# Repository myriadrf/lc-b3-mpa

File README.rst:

LibreCellular LTE Band 3 Medium Power Amplifier
===============================================

.. image:: https://raw.githubusercontent.com/myriadrf/lc-b3-mpa/main/images/B3MPA_0p1_PCB_1_1280w.jpg
   :alt: Detail of CI hardware.

This repository contains the PCB (KiCAD) and mechanical designs (STEP) for the LTE Band 3 Medium Power Amplifier.

For further details see the `LibreCellular Documentation`_.

Licence
-------

LibreCellular LTE Band 3 Medium Power Amplifier is copyright 2022 AB Open Ltd and provided under the Solderpad Hardware License v2.1.

.. _LibreCellular Documentation: https://librecellular.org/developer/hardware/rf/b3mpa.html

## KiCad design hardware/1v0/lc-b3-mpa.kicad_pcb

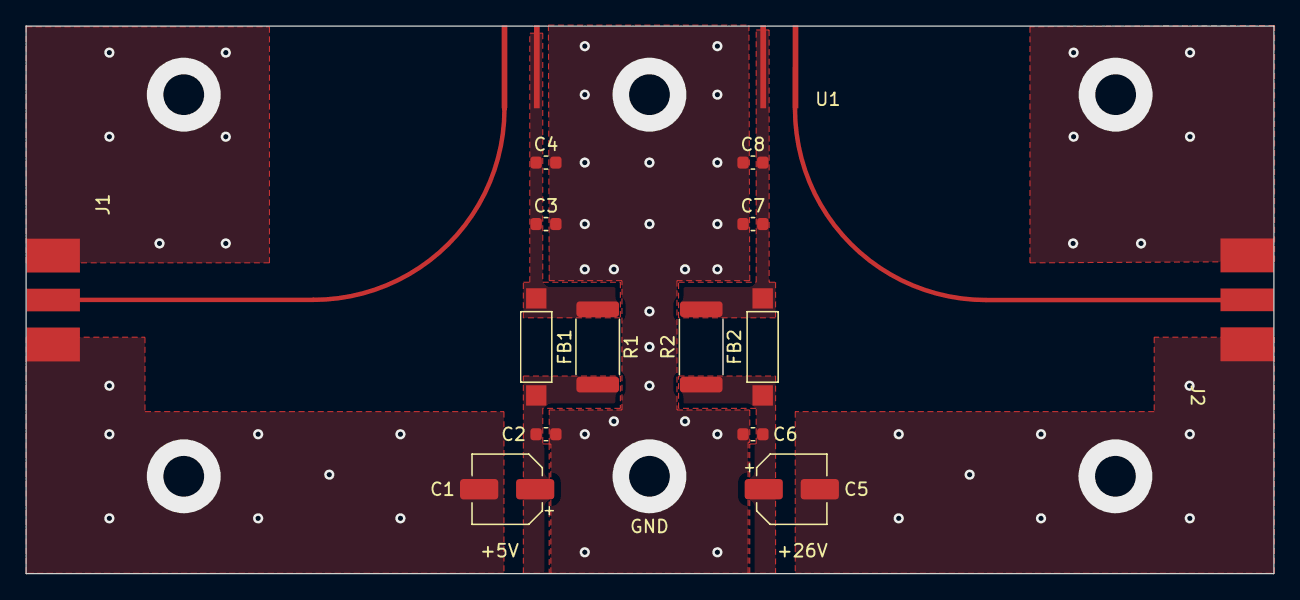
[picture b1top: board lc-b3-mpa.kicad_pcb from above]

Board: 4 copper layers, 98.0 x 43.0 mm, 15 parts (0 on the bottom side), 7 nets.

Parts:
C1, C5: 10uF; CP_Elec_5x5.4
C2, C6: 10nF; C_0603_1608Metric
C3, C7: 100pF; C_0603_1608Metric
C4, C8: 10pF; C_0603_1608Metric
FB1, FB2: FB; L_Axial_L5.3mm_D2.2mm_P7.62mm_Horizontal_Vishay_IM-1
J1, J2: Molex 732512120; Molex_73251-2120
R1, R2: 10R; R_2512_6332Metric
U1: BGY2016

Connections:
+5V: C1.1, C2.1, FB1.2, R1.2
+24V: C5.1, C6.2, FB2.1, R2.1
GND: C1.2, C2.2, C3.2, C4.2, C5.2, C6.1, C7.1, C8.1, J1.2 (Ext), J2.2 (Ext)
unnamed: J1.1 (In), U1.1 (RFin)
unnamed: J2.1 (In), U1.4 (RFout)
unnamed: C3.1, C4.1, FB1.1, R1.1, U1.2 (VS1)
unnamed: C7.2, C8.2, FB2.2, R2.2, U1.3 (VS2)

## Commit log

2022-08-26 Initial commit
    - Add PCB data
    - Add mechanical data
2022-09-02 Add licence and README
2023-08-11 Add 1v0 hardware design
2024-01-13 Update README.rst
    Fix typo.
